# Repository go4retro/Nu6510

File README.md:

# 6510/8500 to 6502 Adapter Schematic and Printed Circuit Board
This PCB will allow a 65(c)02 CPU to emulate a CSG/MOS 6510/8500 CPU.

## Theory
The 6502 address, data, and r/w lines are fed through the CPLD so they can be optionally tri-stated, and the on-board PIO port lines 0-5 are emulated.

## License
Copyright (C) 2019  Jim Brain, RETRO Innovations

These files are free designs; you can redistribute them and/or modify
them under the terms of the Creative Commons Attribution-ShareAlike 
4.0 International License.

You should have received a copy of the license along with this
work. If not, see <http://creativecommons.org/licenses/by-sa/4.0/>.

These files are distributed in the hope that they will be useful,
but WITHOUT ANY WARRANTY; without even the implied warranty of
MERCHANTABILITY or FITNESS FOR A PARTICULAR PURPOSE.  See the
license for more details.

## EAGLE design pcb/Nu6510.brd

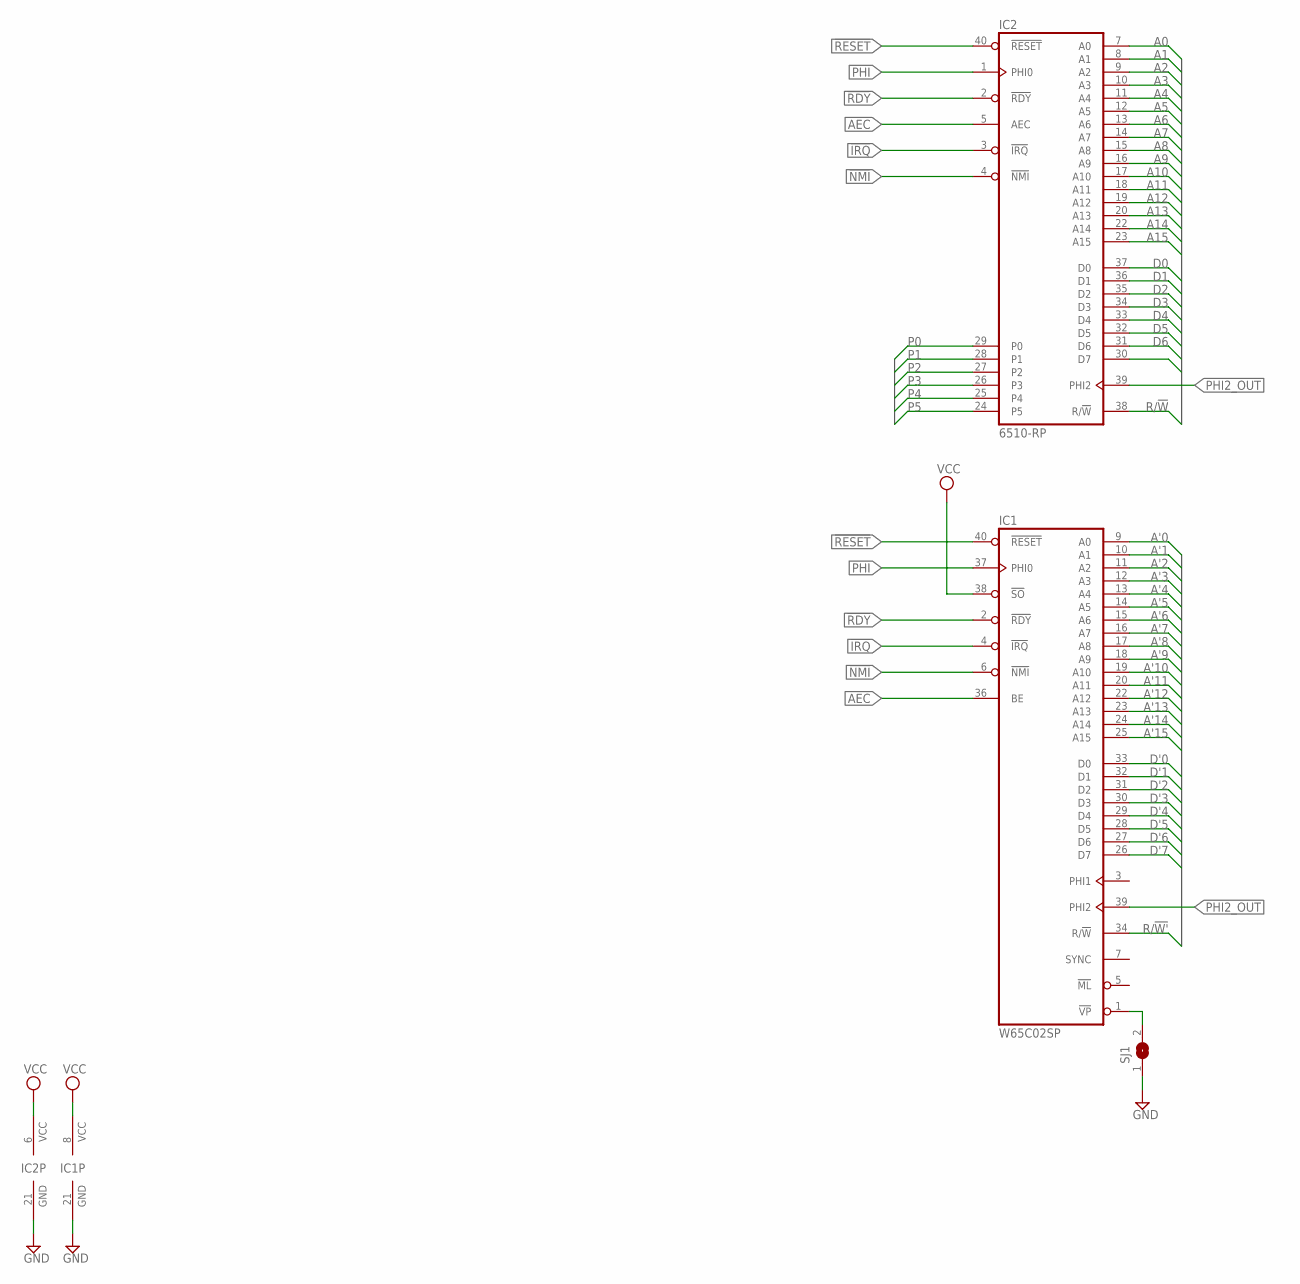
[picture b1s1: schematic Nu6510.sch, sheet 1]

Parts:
IC1: W65C02SP; DIL40-ROUNDPAD
IC2: 6510-RP; DIL40-ROUNDPAD
SJ1: SJ

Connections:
!IRQ: IC1.4 (!IRQ), IC2.3 (!IRQ); also elsewhere on the board
!NMI: IC1.6 (!NMI), IC2.4 (!NMI); also elsewhere on the board
!RDY: IC1.2 (!RDY), IC2.2 (!RDY); also elsewhere on the board
!RESET: IC1.40 (!RESET), IC2.40 (!RESET); also elsewhere on the board
A0: IC2.7 (A0); also elsewhere on the board
A1: IC2.8 (A1); also elsewhere on the board
A2: IC2.9 (A2); also elsewhere on the board
A3: IC2.10 (A3); also elsewhere on the board
A4: IC2.11 (A4); also elsewhere on the board
A5: IC2.12 (A5); also elsewhere on the board
A6: IC2.13 (A6); also elsewhere on the board
A7: IC2.14 (A7); also elsewhere on the board
A8: IC2.15 (A8); also elsewhere on the board
A9: IC2.16 (A9); also elsewhere on the board
A10: IC2.17 (A10); also elsewhere on the board
A11: IC2.18 (A11); also elsewhere on the board
A12: IC2.19 (A12); also elsewhere on the board
A13: IC2.20 (A13); also elsewhere on the board
A14: IC2.22 (A14); also elsewhere on the board
A15: IC2.23 (A15); also elsewhere on the board
A'0: IC1.9 (A0); also elsewhere on the board
A'1: IC1.10 (A1); also elsewhere on the board
A'2: IC1.11 (A2); also elsewhere on the board
A'3: IC1.12 (A3); also elsewhere on the board
A'4: IC1.13 (A4); also elsewhere on the board
A'5: IC1.14 (A5); also elsewhere on the board
A'6: IC1.15 (A6); also elsewhere on the board
A'7: IC1.16 (A7); also elsewhere on the board
A'8: IC1.17 (A8); also elsewhere on the board
A'9: IC1.18 (A9); also elsewhere on the board
A'10: IC1.19 (A10); also elsewhere on the board
A'11: IC1.20 (A11); also elsewhere on the board
A'12: IC1.22 (A12); also elsewhere on the board
A'13: IC1.23 (A13); also elsewhere on the board
A'14: IC1.24 (A14); also elsewhere on the board
A'15: IC1.25 (A15); also elsewhere on the board
AEC: IC1.36 (BE), IC2.5 (AEC); also elsewhere on the board
D0: IC2.37 (D0); also elsewhere on the board
D1: IC2.36 (D1); also elsewhere on the board
D2: IC2.35 (D2); also elsewhere on the board
D3: IC2.34 (D3); also elsewhere on the board
D4: IC2.33 (D4); also elsewhere on the board
D5: IC2.32 (D5); also elsewhere on the board
D6: IC2.31 (D6); also elsewhere on the board
D7: IC2.30 (D7); also elsewhere on the board
D'0: IC1.33 (D0); also elsewhere on the board
D'1: IC1.32 (D1); also elsewhere on the board
D'2: IC1.31 (D2); also elsewhere on the board
D'3: IC1.30 (D3); also elsewhere on the board
D'4: IC1.29 (D4); also elsewhere on the board
D'5: IC1.28 (D5); also elsewhere on the board
D'6: IC1.27 (D6); also elsewhere on the board
D'7: IC1.26 (D7); also elsewhere on the board
GND: IC1.21 (GND), IC2.21 (GND), SJ1.1; also elsewhere on the board
unnamed: IC1.1 (!VP), SJ1.2
P0: IC2.29 (P0); also elsewhere on the board
P1: IC2.28 (P1); also elsewhere on the board
P2: IC2.27 (P2); also elsewhere on the board
P3: IC2.26 (P3); also elsewhere on the board
P4: IC2.25 (P4); also elsewhere on the board
P5: IC2.24 (P5); also elsewhere on the board
PHI: IC1.37 (PHI0), IC2.1 (PHI0); also elsewhere on the board
PHI2_OUT: IC1.39 (PHI2), IC2.39 (PHI2)
R/!W: IC2.38 (R/!W); also elsewhere on the board
R/!W': IC1.34 (R/!W); also elsewhere on the board
VCC: IC1.8 (VCC), IC1.38 (!SO), IC2.6 (VCC); also elsewhere on the board

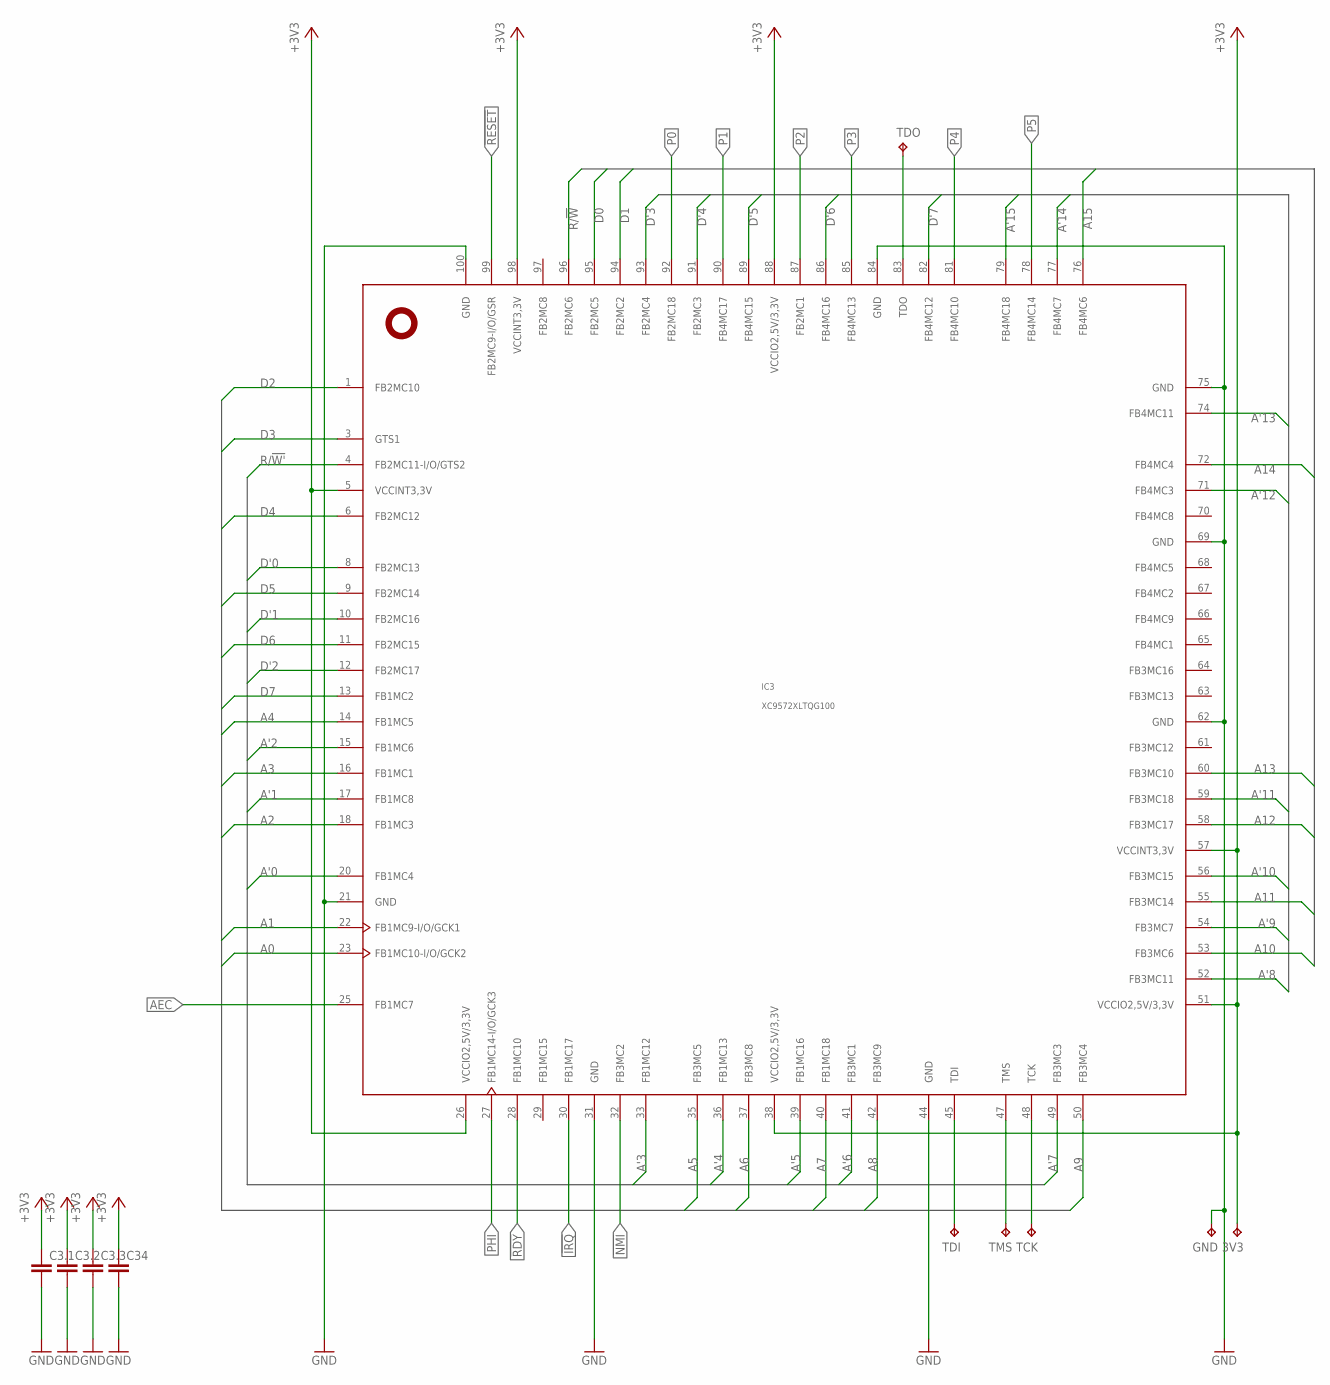
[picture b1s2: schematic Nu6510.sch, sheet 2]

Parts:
3V3: TPTP10SQ; TP10SQ
C3.1, C3.2, C3.3, C34: C-EUC0402; C0402
GND: TPTP10SQ; TP10SQ
IC3: XC9572XLTQG100; TQFP100
TCK: TPTP10SQ; TP10SQ
TDI: TPTP10SQ; TP10SQ
TDO: TPTP10SQ; TP10SQ
TMS: TPTP10SQ; TP10SQ

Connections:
!IRQ: IC3.30 (FB1MC17); also elsewhere on the board
!NMI: IC3.32 (FB3MC2); also elsewhere on the board
!RDY: IC3.28 (FB1MC10); also elsewhere on the board
!RESET: IC3.99 (FB2MC9-I/O/GSR); also elsewhere on the board
+3V3: 3V3.TP, C3.1.1, C3.2.1, C3.3.1, C34.1, IC3.5 (VCCINT3,3V), IC3.26 (VCCIO2,5V/3,3V), IC3.38 (VCCIO2,5V/3,3V), IC3.51 (VCCIO2,5V/3,3V), IC3.57 (VCCINT3,3V), IC3.88 (VCCIO2,5V/3,3V), IC3.98 (VCCINT3,3V); also elsewhere on the board
A0: IC3.23 (FB1MC10-I/O/GCK2); also elsewhere on the board
A1: IC3.22 (FB1MC9-I/O/GCK1); also elsewhere on the board
A2: IC3.18 (FB1MC3); also elsewhere on the board
A3: IC3.16 (FB1MC1); also elsewhere on the board
A4: IC3.14 (FB1MC5); also elsewhere on the board
A5: IC3.35 (FB3MC5); also elsewhere on the board
A6: IC3.37 (FB3MC8); also elsewhere on the board
A7: IC3.40 (FB1MC18); also elsewhere on the board
A8: IC3.42 (FB3MC9); also elsewhere on the board
A9: IC3.50 (FB3MC4); also elsewhere on the board
A10: IC3.53 (FB3MC6); also elsewhere on the board
A11: IC3.55 (FB3MC14); also elsewhere on the board
A12: IC3.58 (FB3MC17); also elsewhere on the board
A13: IC3.60 (FB3MC10); also elsewhere on the board
A14: IC3.72 (FB4MC4); also elsewhere on the board
A15: IC3.76 (FB4MC6); also elsewhere on the board
A'0: IC3.20 (FB1MC4); also elsewhere on the board
A'1: IC3.17 (FB1MC8); also elsewhere on the board
A'2: IC3.15 (FB1MC6); also elsewhere on the board
A'3: IC3.33 (FB1MC12); also elsewhere on the board
A'4: IC3.36 (FB1MC13); also elsewhere on the board
A'5: IC3.39 (FB1MC16); also elsewhere on the board
A'6: IC3.41 (FB3MC1); also elsewhere on the board
A'7: IC3.49 (FB3MC3); also elsewhere on the board
A'8: IC3.52 (FB3MC11); also elsewhere on the board
A'9: IC3.54 (FB3MC7); also elsewhere on the board
A'10: IC3.56 (FB3MC15); also elsewhere on the board
A'11: IC3.59 (FB3MC18); also elsewhere on the board
A'12: IC3.71 (FB4MC3); also elsewhere on the board
A'13: IC3.74 (FB4MC11); also elsewhere on the board
A'14: IC3.77 (FB4MC7); also elsewhere on the board
A'15: IC3.79 (FB4MC18); also elsewhere on the board
AEC: IC3.25 (FB1MC7); also elsewhere on the board
D0: IC3.95 (FB2MC5); also elsewhere on the board
D1: IC3.94 (FB2MC2); also elsewhere on the board
D2: IC3.1 (FB2MC10); also elsewhere on the board
D3: IC3.3 (GTS1); also elsewhere on the board
D4: IC3.6 (FB2MC12); also elsewhere on the board
D5: IC3.9 (FB2MC14); also elsewhere on the board
D6: IC3.11 (FB2MC15); also elsewhere on the board
D7: IC3.13 (FB1MC2); also elsewhere on the board
D'0: IC3.8 (FB2MC13); also elsewhere on the board
D'1: IC3.10 (FB2MC16); also elsewhere on the board
D'2: IC3.12 (FB2MC17); also elsewhere on the board
D'3: IC3.93 (FB2MC4); also elsewhere on the board
D'4: IC3.91 (FB2MC3); also elsewhere on the board
D'5: IC3.89 (FB4MC15); also elsewhere on the board
D'6: IC3.86 (FB4MC16); also elsewhere on the board
D'7: IC3.82 (FB4MC12); also elsewhere on the board
GND: C3.1.2, C3.2.2, C3.3.2, C34.2, GND.TP, IC3.21 (GND), IC3.31 (GND), IC3.44 (GND), IC3.62 (GND), IC3.69 (GND), IC3.75 (GND), IC3.84 (GND), IC3.100 (GND); also elsewhere on the board
unnamed: IC3.48 (TCK), TCK.TP
unnamed: IC3.47 (TMS), TMS.TP
unnamed: IC3.45 (TDI), TDI.TP
unnamed: IC3.83 (TDO), TDO.TP
P0: IC3.92 (FB2MC18); also elsewhere on the board
P1: IC3.90 (FB4MC17); also elsewhere on the board
P2: IC3.87 (FB2MC1); also elsewhere on the board
P3: IC3.85 (FB4MC13); also elsewhere on the board
P4: IC3.81 (FB4MC10); also elsewhere on the board
P5: IC3.78 (FB4MC14); also elsewhere on the board
PHI: IC3.27 (FB1MC14-I/O/GCK3); also elsewhere on the board
R/!W: IC3.96 (FB2MC6); also elsewhere on the board
R/!W': IC3.4 (FB2MC11-I/O/GTS2); also elsewhere on the board

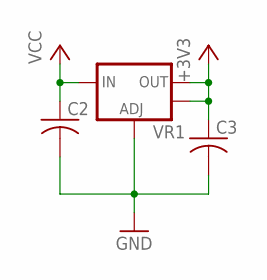
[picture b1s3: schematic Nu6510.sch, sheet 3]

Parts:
C2, C3: C-USC0805; C0805
VR1: V_REG_LM1117SOT223; SOT223

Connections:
+3V3: C3.1, VR1.2 (OUT), VR1.4 (OUT); also elsewhere on the board
GND: C2.2, C3.2, VR1.1 (ADJ); also elsewhere on the board
VCC: C2.1, VR1.3 (IN); also elsewhere on the board

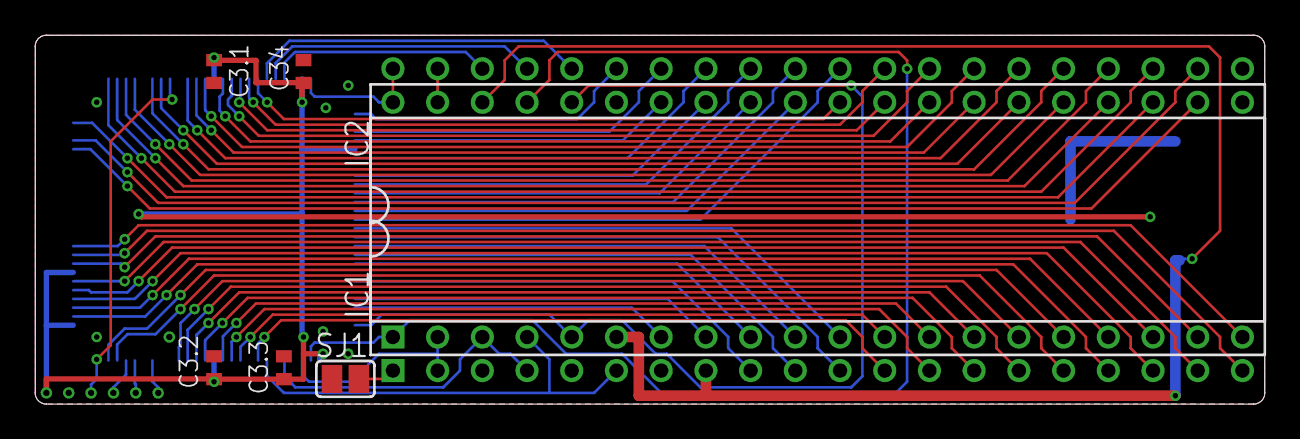
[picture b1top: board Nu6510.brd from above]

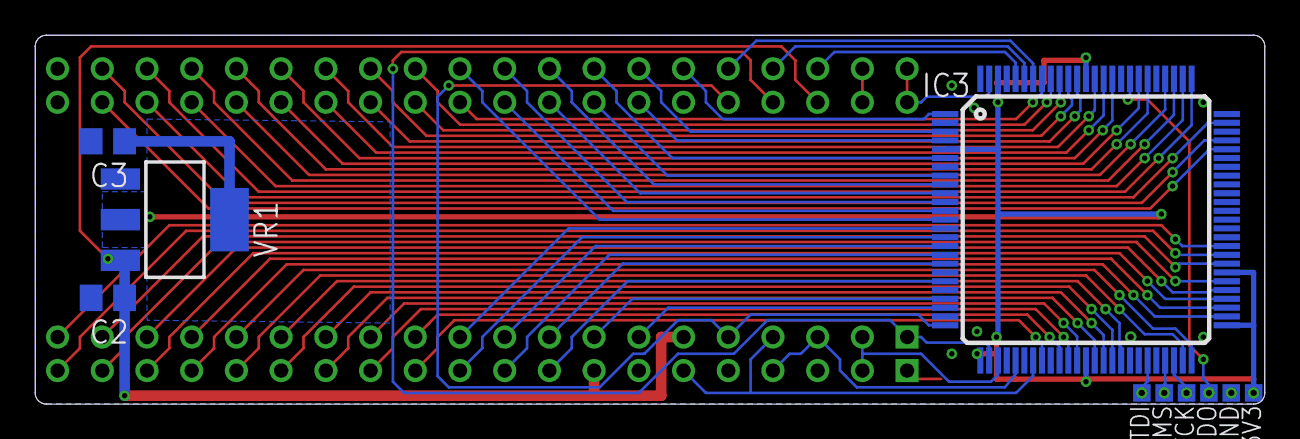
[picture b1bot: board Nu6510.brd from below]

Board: 2 copper layers, 69.8 x 21.0 mm, 17 parts (10 on the bottom side), 71 nets.

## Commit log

2019-10-03 Fix typo
2019-11-26 Support reading and writing all 8 bits of the IO register

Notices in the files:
parts and their libraries:
SparkFun: Licensing: CC v3.0 Share-Alike You are welcome to use this library for commercial purposes.
